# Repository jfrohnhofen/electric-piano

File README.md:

# Electric Piano

This repository contains the hardware and software sources for a custom electric piano project built around the ATmega16 microcontroller.

## Project Structure

The project is divided into the following main directories:

- **circuit/**: Contains the hardware design files.
  - `eagle/`: Schematics and PCB layouts designed in EAGLE.
  - `gerber/`: Manufacturing files for the PCB.
  - `parts.txt`: Bill of materials (BOM).
  - `stencil.svg`: Stencil design for solder paste application.

- **firmware/**: The C++ firmware running on the ATmega16 (16MHz).
  - `firmware.cpp`: Main application code.
  - `bootloader.cpp`: Custom bootloader.
  - `runfile`: Build and flash instructions using `avr-g++` and `avrdude` via STK500v1 over serial.

- **programer/**: A custom programmer utility written in Rust.

## Prerequisites

The easiest way to get started is by using the provided Nix flake. If you have [Nix](https://nixos.org/) installed, simply run:

```bash
nix develop
```

This will drop you into a development shell with all the required dependencies (`avr-gcc`, `avrdude`, `cargo`, `just`, etc.) installed.

If you are not using Nix, you will need to manually install:
- `avr-gcc` / `avr-g++`
- `avr-libc`
- `avrdude`
- Rust toolchain (`cargo`)
- [`just`](https://github.com/casey/just) command runner

## Building and Flashing

This project uses `just` as a command runner. You can see all available commands by running:

```bash
just --list
```

From the root directory, you can run:

- Compile the bootloader: `just bootloader`
- Compile the firmware: `just firmware`
- Flash the bootloader: `just flash-bootloader`
- Write fuses: `just write-fuses`
- Build the Rust programmer: `just build-programmer`
- Run the Rust programmer: `just run-programmer`
- Build everything: `just build-all`

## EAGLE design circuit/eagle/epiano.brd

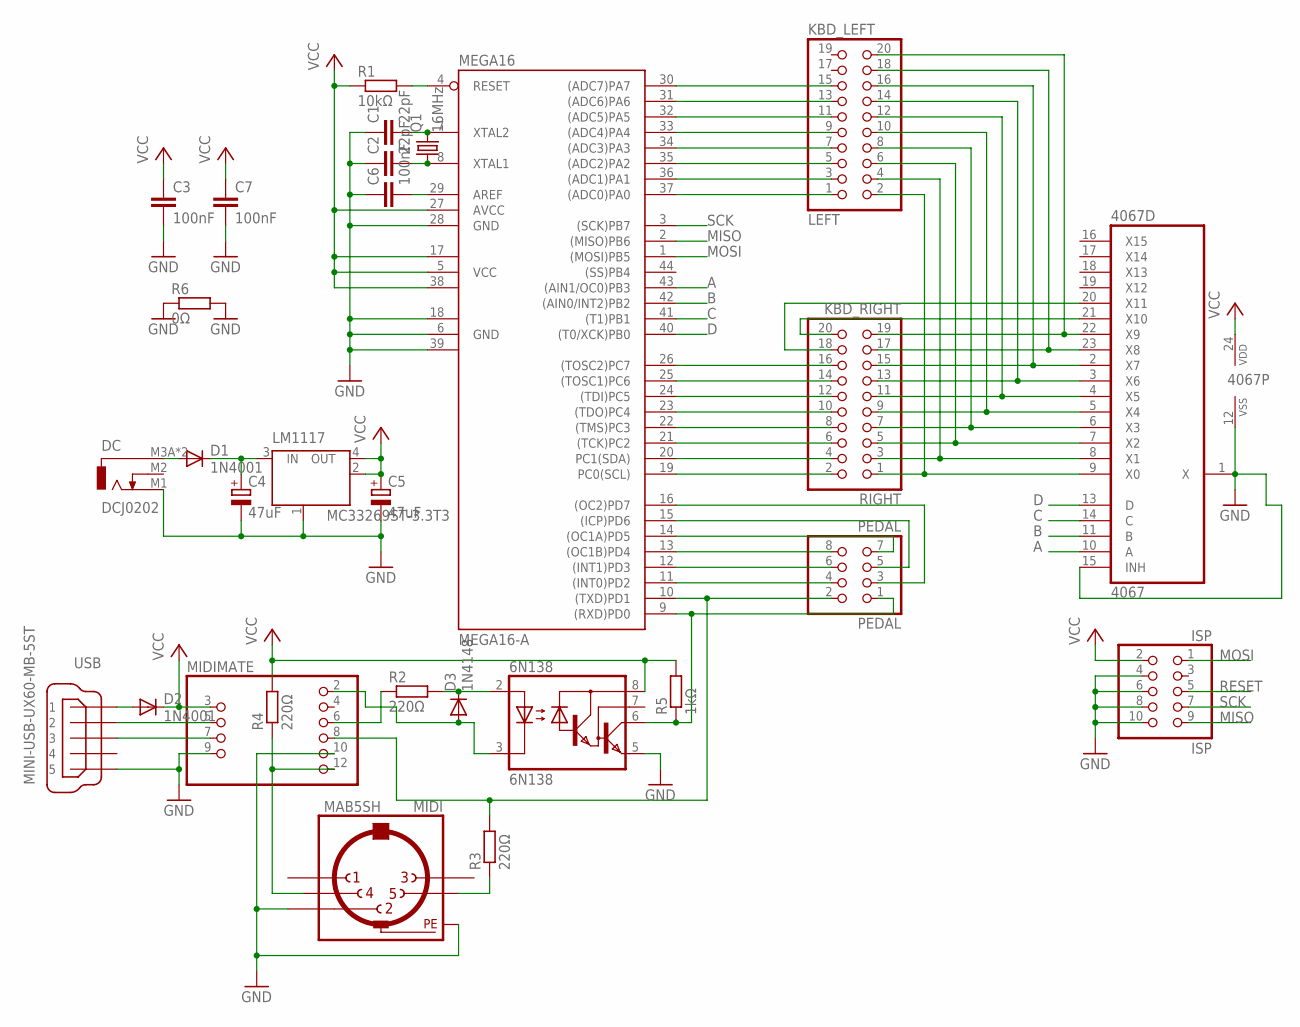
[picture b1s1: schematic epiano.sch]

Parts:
6N138: 6N138; SMD-8
4067: 4067D; SO24W
C1, C2: 22pF; C0805
C3, C6, C7: 100nF; C0805
C4, C5: 47uF; PANASONIC_D
D1, D2: 1N4001; MELF-MLL41
D3: 1N4148; MINIMELF
DC: DCJ0202
ISP: ISP; 2X05SMD
LEFT: KBD_LEFT; 2X10SMD
LM1117: MC33269ST-3.3T3; SOT223
MEGA16: MEGA16-A; TQFP44
MIDI: MAB5SH
MIDIMATE: USBMIDI_2.54-SMD; USBMIDI
PEDAL: PEDAL; 2X04SMD
Q1: 16MHz; SM49
R1: 10kΩ; R0805
R2, R3, R4: 220Ω; R0805
R5: 1kΩ; R0805
R6: 0Ω; R1206
RIGHT: KBD_RIGHT; 2X10SMD
USB: MINI-USB-UX60-MB-5ST; UX60-MB-5ST

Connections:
A: 4067.10 (A), MEGA16.43 ((AIN1/OC0)PB3)
B: 4067.11 (B), MEGA16.42 ((AIN0/INT2)PB2)
C: 4067.14 (C), MEGA16.41 ((T1)PB1)
D: 4067.13 (D), MEGA16.40 ((T0/XCK)PB0)
GND: 6N138.5 (GND), 4067.1 (X), 4067.12 (VSS), 4067.15 (INH), C1.1, C2.1, C3.2, C4.-, C5.-, C6.1, C7.2, DC.M1 (3), ISP.4, ISP.6, ISP.8, ISP.10, LM1117.1 (GND/ADJ), MEGA16.6 (GND), MEGA16.18 (GND1), MEGA16.28 (GND), MEGA16.39 (GND2), MIDI.2, MIDI.PE, MIDI.PE@ (PE), MIDIMATE.9, MIDIMATE.10, R6.1, R6.2, USB.5
MISO: ISP.9, MEGA16.2 ((MISO)PB6)
MOSI: ISP.1, MEGA16.1 ((MOSI)PB5)
unnamed: D2.A, USB.1
unnamed: MIDIMATE.5, USB.2
unnamed: C2.2, MEGA16.8 (XTAL1), Q1.1
unnamed: C4.+, D1.C, LM1117.3 (IN)
unnamed: MEGA16.19 (PC0(SCL)), RIGHT.2
unnamed: MEGA16.20 (PC1(SDA)), RIGHT.4
unnamed: MEGA16.21 ((TCK)PC2), RIGHT.6
unnamed: D1.A, DC.M3A (1), DC.M3B (1)
unnamed: MEGA16.22 ((TMS)PC3), RIGHT.8
unnamed: MEGA16.23 ((TDO)PC4), RIGHT.10
unnamed: MEGA16.24 ((TDI)PC5), RIGHT.12
unnamed: MEGA16.25 ((TOSC1)PC6), RIGHT.14
unnamed: MEGA16.26 ((TOSC2)PC7), RIGHT.16
unnamed: 4067.20 (X11), RIGHT.18
unnamed: LEFT.1, MEGA16.37 ((ADC0)PA0)
unnamed: LEFT.3, MEGA16.36 ((ADC1)PA1)
unnamed: LEFT.5, MEGA16.35 ((ADC2)PA2)
unnamed: LEFT.7, MEGA16.34 ((ADC3)PA3)
unnamed: LEFT.9, MEGA16.33 ((ADC4)PA4)
unnamed: LEFT.11, MEGA16.32 ((ADC5)PA5)
unnamed: LEFT.13, MEGA16.31 ((ADC6)PA6)
unnamed: LEFT.15, MEGA16.30 ((ADC7)PA7)
unnamed: 4067.21 (X10), RIGHT.20
unnamed: 4067.9 (X0), LEFT.2, RIGHT.1
unnamed: 4067.8 (X1), LEFT.4, RIGHT.3
unnamed: 4067.7 (X2), LEFT.6, RIGHT.5
unnamed: 4067.6 (X3), LEFT.8, RIGHT.7
unnamed: 4067.5 (X4), LEFT.10, RIGHT.9
unnamed: 4067.4 (X5), LEFT.12, RIGHT.11
unnamed: 4067.3 (X6), LEFT.14, RIGHT.13
unnamed: 4067.2 (X7), LEFT.16, RIGHT.15
unnamed: 4067.23 (X8), LEFT.18, RIGHT.17
unnamed: 4067.22 (X9), LEFT.20, RIGHT.19
unnamed: MEGA16.10 ((TXD)PD1), MIDIMATE.8, PEDAL.2, R3.2
unnamed: C6.2, MEGA16.29 (AREF)
unnamed: MEGA16.11 ((INT0)PD2), PEDAL.4
unnamed: MEGA16.12 ((INT1)PD3), PEDAL.6
unnamed: C1.2, MEGA16.7 (XTAL2), Q1.2
unnamed: MIDIMATE.7, USB.3
unnamed: MIDIMATE.6, R2.1
unnamed: MEGA16.13 ((OC1B)PD4), PEDAL.8
unnamed: MIDI.4, MIDIMATE.12, R4.1
unnamed: 6N138.3 (C), D3.A, MIDIMATE.2
unnamed: MEGA16.14 ((OC1A)PD5), PEDAL.7
unnamed: MEGA16.15 ((ICP)PD6), PEDAL.5
unnamed: MEGA16.16 ((OC2)PD7), PEDAL.3
unnamed: MIDI.5, R3.1
unnamed: 6N138.2 (A), D3.C, R2.2
unnamed: 6N138.6 (VO), MEGA16.9 ((RXD)PD0), PEDAL.1, R5.1
RESET: ISP.5, MEGA16.4 (RESET), R1.2
SCK: ISP.7, MEGA16.3 ((SCK)PB7)
VCC: 6N138.8 (VCC), 4067.24 (VDD), C3.1, C5.+, C7.1, D2.C, ISP.2, LM1117.2 (OUT), LM1117.4 (OUT), MEGA16.5 (VCC), MEGA16.17 (VCC1), MEGA16.27 (AVCC), MEGA16.38 (VCC2), MIDIMATE.3, R1.1, R4.2, R5.2

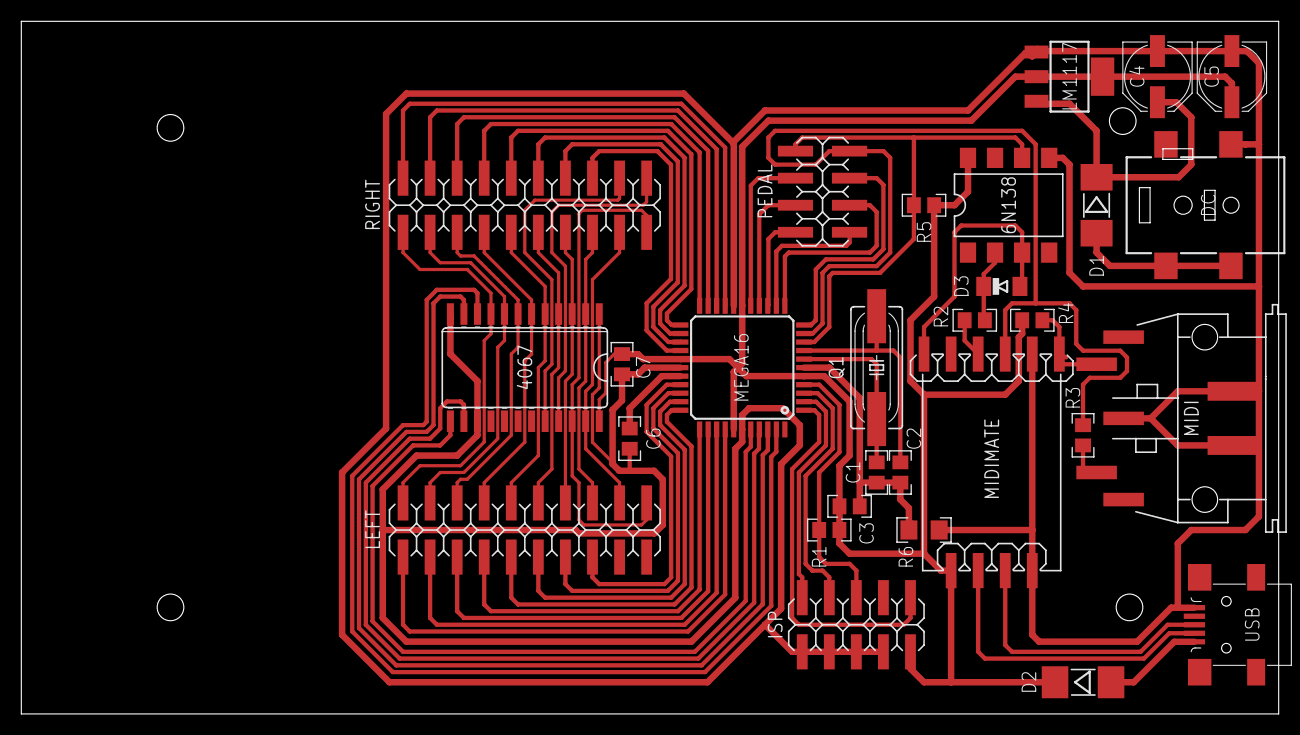
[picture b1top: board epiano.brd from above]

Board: 1 copper layer, 118.0 x 65.0 mm, 29 parts (0 on the bottom side), 59 nets.

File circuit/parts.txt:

Partlist

Exported from epiano.sch at 8/28/2015 8:06 PM

EAGLE Version 7.3.0 Copyright (c) 1988-2015 CadSoft

Assembly variant: 

Part     Value                Device               Package     Library  Sheet

6N138    6N138                6N138                SMD-8       epiano   1
4067     4067D                4067D                SO24W       40xx     1
C1       22pF                 C-EUC0805            C0805       epiano   1
C2       22pF                 C-EUC0805            C0805       epiano   1
C3       100nF                C-EUC0805            C0805       epiano   1
C4       47uF                 CPOL-EUD             PANASONIC_D rcl      1
C5       47uF                 CPOL-EUD             PANASONIC_D rcl      1
C6       100nF                C-EUC0805            C0805       epiano   1
C7       100nF                C-EUC0805            C0805       epiano   1
D1       1N4001               DIODE-MELF-MLL41     MELF-MLL41  diode    1
D2       1N4001               DIODE-MELF-MLL41     MELF-MLL41  diode    1
D3       1N4148               DIODE-MINIMELF       MINIMELF    diode    1
DC       DCJ0202              DCJ0202              DCJ0202     epiano   1
ISP      ISP                  PINHD-2X5_2.54-SMD   2X05SMD     epiano   1
LEFT     KBD_LEFT             PINHD-2X10_2.54-SMD  2X10SMD     epiano   1
LM1117   MC33269ST-3.3T3      MC33269ST-3.3T3      SOT223      epiano   1
MEGA16   MEGA16-A             MEGA16-A             TQFP44      atmel    1
MIDI     MAB5SH               MAB5SH               MAB5SH      epiano   1
MIDIMATE                      USBMIDI_2.54-SMD     USBMIDI     epiano   1
PEDAL    PEDAL                PINHD-2X4_2.54-SMD   2X04SMD     epiano   1
Q1       16MHz                CRYSTALSM49          SM49        crystal  1
R1       10k?                 R-EU_R0805           R0805       epiano   1
R2       220?                 R-EU_R0805           R0805       epiano   1
R3       220?                 R-EU_R0805           R0805       epiano   1
R4       220?                 R-EU_R0805           R0805       epiano   1
R5       1k?                  R-EU_R0805           R0805       epiano   1
R6       0?                   R-EU_R1206           R1206       epiano   1
RIGHT    KBD_RIGHT            PINHD-2X10_2.54-SMD  2X10SMD     epiano   1
USB      MINI-USB-UX60-MB-5ST MINI-USB-UX60-MB-5ST UX60-MB-5ST epiano   1

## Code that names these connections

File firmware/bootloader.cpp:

// The MIT License (MIT)
//
// Copyright (c) 2016 Johannes Frohnhofen
//
// Permission is hereby granted, free of charge, to any person obtaining a copy
// of this software and associated documentation files (the "Software"), to deal
// in the Software without restriction, including without limitation the rights
// to use, copy, modify, merge, publish, distribute, sublicense, and/or sell
// copies of the Software, and to permit persons to whom the Software is
// furnished to do so, subject to the following conditions:
//
// The above copyright notice and this permission notice shall be included in
// all copies or substantial portions of the Software.
//
// THE SOFTWARE IS PROVIDED "AS IS", WITHOUT WARRANTY OF ANY KIND, EXPRESS OR
// IMPLIED, INCLUDING BUT NOT LIMITED TO THE WARRANTIES OF MERCHANTABILITY,
// FITNESS FOR A PARTICULAR PURPOSE AND NONINFRINGEMENT. IN NO EVENT SHALL THE
// AUTHORS OR COPYRIGHT HOLDERS BE LIABLE FOR ANY CLAIM, DAMAGES OR OTHER
// LIABILITY, WHETHER IN AN ACTION OF CONTRACT, TORT OR OTHERWISE, ARISING FROM,
// OUT OF OR IN CONNECTION WITH THE SOFTWARE OR THE USE OR OTHER DEALINGS IN
// THE SOFTWARE.
//
// -----------------------------------------------------------------------------
//

#include <avr/boot.h>
#include <avr/interrupt.h>
#include <avr/io.h>
#include <avr/pgmspace.h>
#include <util/delay.h>
#include <stdbool.h>

#define BAUD_RATE 31250
#define NUM_PAGES ((FLASHEND + 1) / SPM_PAGESIZE)
#define MIDI_ID   0x70
#define VERSION   0x01

//////////////

#define CHECK(EXPR, ERR) \
  if(!(EXPR)) { \
    reply_error(ERR); \
    break; \
  }

typedef enum {
  STATE_IDLE,
  STATE_MATCHING_HEADER,
  STATE_READING_BODY,
  STATE_EXPECTING_END
} state_t;

typedef enum {
  COMMAND_PING   = 0x10,
  COMMAND_WRITE  = 0x11,
  COMMAND_READ   = 0x12,
  COMMAND_VERIFY = 0x13,
  COMMAND_QUIT   = 0x14,

  REPLY_SUCCESS  = 0x20,
  REPLY_ERROR    = 0x21,
  REPLY_READ     = 0x22,
  REPLY_VERIFY   = 0x23
} command_t;

typedef enum {
  ERROR_NONE,
  ERROR_HEADER_MISMATCH,
  ERROR_INVALID_FORMAT,
  ERROR_INCOMPLETE_MESSAGE,
  ERROR_INVALID_NIBBLE,
  ERROR_INVALID_CHECKSUM,
  ERROR_UNKNOWN_COMMAND,
  ERROR_INVALID_PAYLOAD_SIZE,
  ERROR_INVALID_PAGE_NUMBER
} error_t;

typedef struct {
  uint8_t header[3];
  union {
    struct {
      uint8_t command;
      union {
        uint8_t checksum;
        uint8_t error;
        struct {
          uint8_t page_no;
          uint8_t page_data[SPM_PAGESIZE];
        };
      };
    };
    uint8_t buffer[SPM_PAGESIZE + sizeof(page_no) + sizeof(command) + 1];
  };
} message_t;

void (*program_main)(void) = 0x0000;

state_t   state;
message_t msg;
uint16_t  payload_size;

inline bool bootloader_active()
{
  DDRD  = _BV(PD5) | _BV(PD6);
  PORTD = _BV(PD3) | _BV(PD4);

  _delay_us(10);

  return !(PIND & (_BV(PD3) | _BV(PD4)));
}

//// UART ////

inline void uart_init()
{
  uint16_t baud = (((F_CPU) + 8UL * (BAUD_RATE)) / (16UL * (BAUD_RATE)) - 1UL);

  UBRRH = baud >> 8;
  UBRRL = baud;
  UCSRB = _BV(RXEN) | _BV(TXEN);
}

inline uint8_t uart_getc()
{
  while(!(UCSRA & _BV(RXC)));
  return UDR;
}

inline void uart_putc(uint8_t byte)
{
  while(!(UCSRA & _BV(UDRE)));
  UDR = byte;
}

inline void send_msg(uint8_t params_size)
{
  uart_putc(0xf0);

  for(uint8_t i = 0; i < sizeof(msg.header); ++i) {
    uart_putc(msg.header[i]);
  }

  uint8_t checksum = 0;
  uint8_t msg_size = sizeof(msg.command) + params_size;
  for(uint16_t i = 0; i < msg_size; ++i) {
    uart_putc(msg.buffer[i] >> 4);
    uart_putc(msg.buffer[i] & 0x0f);
    checksum ^= msg.buffer[i];
  }

  uart_putc(checksum >> 4);
  uart_putc(checksum & 0x0f);

  uart_putc(0xf7);
}

inline void reply_success()
{
  msg.command = REPLY_SUCCESS;
  send_msg(0);
}

inline void reply_error(uint8_t error)
{
  msg.command = REPLY_ERROR;
  msg.error = error;
  send_msg(sizeof(msg.error));
}

inline void reply_data(command_t command, uint16_t data_size)
{
  msg.command = command;
  send_msg(data_size);
}

// COMMANDS

inline void command_write()
{
  uint32_t page = msg.page_no * SPM_PAGESIZE;
  uint8_t  *buffer = msg.page_data;
  uint16_t w;

  eeprom_busy_wait();

  boot_page_erase(page);
  boot_spm_busy_wait();

  for(uint16_t addr = 0; addr < SPM_PAGESIZE; addr += 2)
  {
    w = *buffer++;
    w += (*buffer++) << 8;
    boot_page_fill(addr, w);
  }

  boot_page_write(page);
  boot_spm_busy_wait();
  boot_rww_enable();
}

inline void command_read()
{
  uint32_t page = msg.page_no * SPM_PAGESIZE;
  uint8_t *buffer = &msg.page_no;

  for(uint16_t addr = page; addr < page + SPM_PAGESIZE; ++addr)
  {
    *buffer++ = pgm_read_byte(addr);
  }
}

inline void command_verify()
{
 uint32_t page = msg.page_no * SPM_PAGESIZE;
  
  msg.checksum = 0;

  for(uint16_t addr = page; addr < page + SPM_PAGESIZE; ++addr)
  {
    msg.checksum ^= pgm_read_byte(addr);
  }
}

inline void process_msg()
{
  switch(msg.command) {
    case COMMAND_PING:
      CHECK(!payload_size, ERROR_INVALID_PAYLOAD_SIZE)
      reply_success();
      break;

    case COMMAND_WRITE:
      CHECK(payload_size == SPM_PAGESIZE + sizeof(msg.page_no),
        ERROR_INVALID_PAYLOAD_SIZE)
      CHECK(msg.page_no < NUM_PAGES, ERROR_INVALID_PAGE_NUMBER)
      command_write();
      reply_success();
      break;

    case COMMAND_VERIFY:
      CHECK(payload_size == sizeof(msg.page_no), ERROR_INVALID_PAYLOAD_SIZE)
      CHECK(msg.page_no < NUM_PAGES, ERROR_INVALID_PAGE_NUMBER)
      command_verify();
      reply_data(REPLY_VERIFY, 1);
      break;

    case COMMAND_READ:
      CHECK(payload_size == sizeof(msg.page_no), ERROR_INVALID_PAYLOAD_SIZE)
      CHECK(msg.page_no < NUM_PAGES, ERROR_INVALID_PAGE_NUMBER)
      command_read();
      reply_data(REPLY_READ, SPM_PAGESIZE);
      break;

    case COMMAND_QUIT:
      CHECK(!payload_size, ERROR_INVALID_PAYLOAD_SIZE)
      reply_success();
      program_main();
      break;

    default:
      reply_error(ERROR_UNKNOWN_COMMAND);
      break;
  }
}

inline void loop()
{
  uint8_t  byte;
  uint8_t  checksum;
  uint16_t bytes_read;

  msg.header[0] = 0x00;
  msg.header[1] = MIDI_ID;
  msg.header[2] = VERSION;
  
  state = STATE_IDLE;

  for(;;) {
    byte = uart_getc();

    if(byte < 0x80) {
      switch(state) {
        case STATE_MATCHING_HEADER:
          if(byte != msg.header[bytes_read++]) {
            reply_error(ERROR_HEADER_MISMATCH);
            state = STATE_IDLE;
          } else if(bytes_read == sizeof(msg.header)) {
            state = STATE_READING_BODY;
            bytes_read = 0;
          }
          break;

        case STATE_READING_BODY:
          if(byte > 0xf) {
            reply_error(ERROR_INVALID_NIBBLE);
            state = STATE_IDLE;
            break;
          }
          if(bytes_read++ & 1) {
            msg.buffer[payload_size] += byte;
            checksum ^= msg.buffer[payload_size++];
          } else {
            msg.buffer[payload_size] = byte << 4;
          }
          if(payload_size == sizeof(msg.buffer)) {
            state = STATE_EXPECTING_END;
          }
          break;

        case STATE_EXPECTING_END:
          reply_error(ERROR_INVALID_PAYLOAD_SIZE);
          state = STATE_IDLE;
          break;
      }
    } else if(byte == 0xf0) {
      if(state != STATE_IDLE) {
        reply_error(ERROR_INCOMPLETE_MESSAGE);
      }
      state = STATE_MATCHING_HEADER;
      checksum = 0;
      bytes_read = 0;
      payload_size = 0;
    } else if(byte == 0xf7) {
      if(state != STATE_IDLE) {
        if(state < STATE_READING_BODY || payload_size <= sizeof(msg.command)) {
          reply_error(ERROR_INVALID_FORMAT);
        } else if(checksum) {
          reply_error(ERROR_INVALID_CHECKSUM);
        } else {
          payload_size -= sizeof(msg.command) + sizeof(checksum);
          process_msg();
        }
        state = STATE_IDLE;
      }
    }

  }
}

int main()
{
  uart_init();

  if(!bootloader_active()) {
    program_main();
  }

  loop();
}

void __init9(void) __attribute__ ((naked)) __attribute__ ((section (".init9")));
void __init9(void)
{   
  asm volatile ( "clr __zero_reg__" );
  asm volatile (
      "ldi r28, lo8(%0)" "\n\t"
      "ldi r29, hi8(%0)" "\n\t"
      "out __SP_L__, r28" "\n\t"
      "out __SP_H__, r29" "\n\t"
      :: "i" (RAMEND)
  );
  asm volatile ( "rjmp main" );
}

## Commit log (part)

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2017-06-07 Added circuit files
2017-06-07 Added gitignore
2017-06-11 Modified gitignore
2017-06-13 Added bootloader and firmware
2017-06-13 Working on sysex-programer
2017-06-13 Modifying gitignore
2017-06-13 Renamed .make to runfile
